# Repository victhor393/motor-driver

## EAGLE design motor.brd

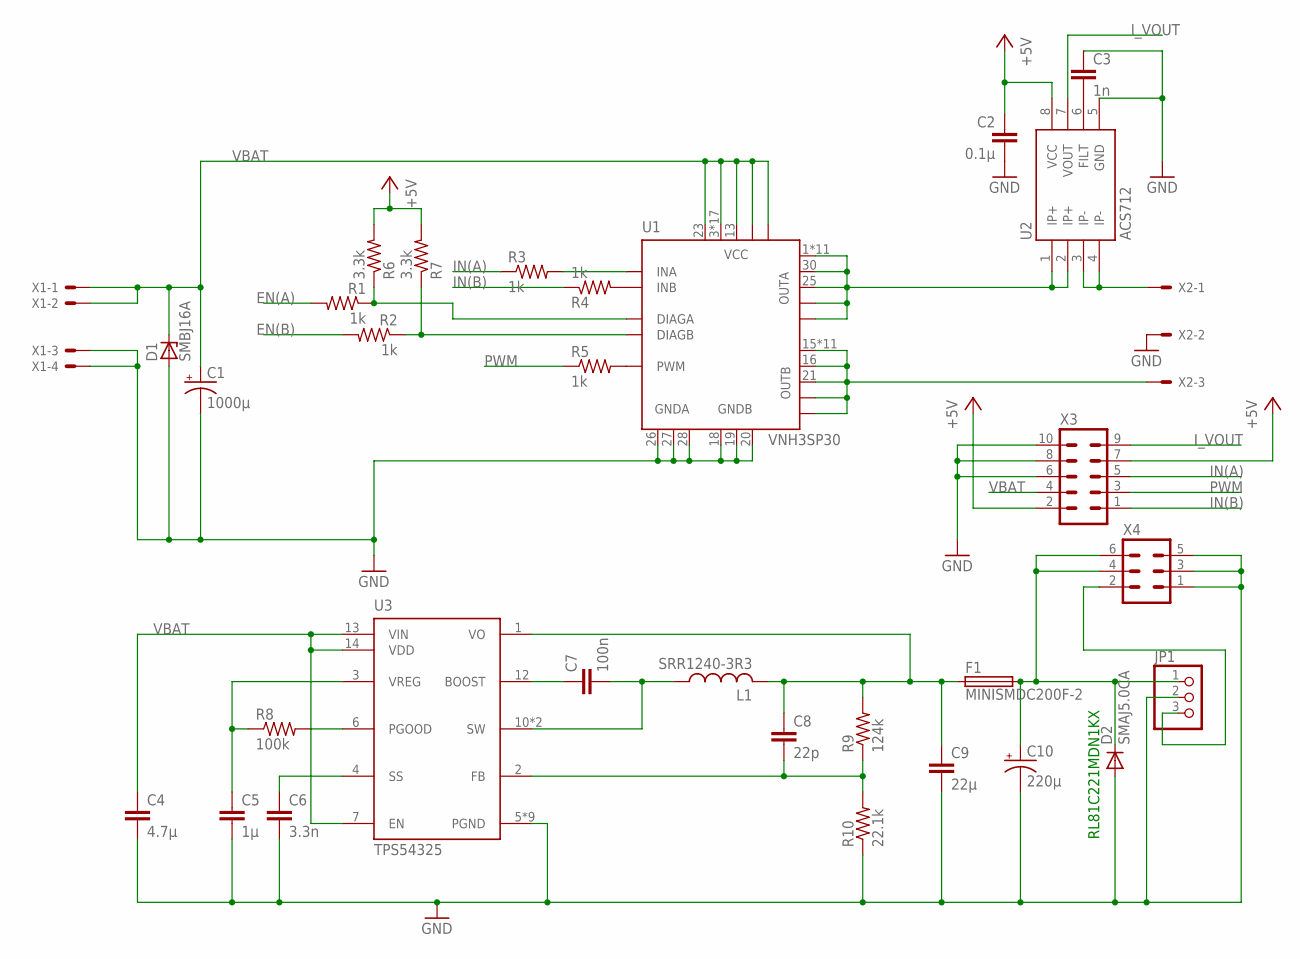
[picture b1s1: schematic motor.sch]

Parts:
C1: 1000µ; E5-13
C2: 0.1µ; C0805
C3: 1n; C0805
C4: 4.7µ; C1206
C5: 1µ; C0805
C6: 3.3n; C0805
C7: 100n; C0805
C8: 22p; C0805
C9: 22µ; C3225
C10: 220µ; E3,5-8
D1: SMBJ16A; SMB
D2: SMAJ5.0CA; DO-214AC
F1: MINISMDC200F-2; MINISMDC200F
JP1: PINHD-1X3; 1X03
L1: SRR1240-3R3; HCM1103
R1, R2, R3, R4, R5: 1k; R0805
R6, R7: 3.3k; R0805
R8: 100k; R0805
R9: 124k; R0805
R10: 22.1k; R0805
U1: VNH3SP30; MULTIPOWERSO-30
U2: ACS712; SO08
U3: TPS54325; HTSSOP14PWP
X1: KK-156-4
X2: KK-156-3
X3: ML10
X4: ML6

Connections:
+5V: C2.1, R6.2, R7.2, U2.8 (VCC), X3.2, X3.7
+5V/S: C8.1, C9.1, F1.1, L1.P$2 (2), R9.2, U3.1 (VO)
EN(A): R1.2
EN(B): R2.2
GND: C1.-, C2.2, C3.1, C4.2, C5.2, C6.2, C9.2, C10.-, D1.A, D2.A, JP1.2, R10.1, U1.18 (GNDB), U1.19 (GNDB), U1.20 (GNDB), U1.26 (GNDA), U1.27 (GNDA), U1.28 (GNDA), U2.5 (GND), U3.5 (PGND), U3.8 (PGND), U3.9 (PGND), U3.EXP (PGND), U3.EXP1 (PGND), U3.P$1 (PGND), U3.P$2 (PGND), U3.P$3 (PGND), U3.P$4 (PGND), X1.3, X1.4, X2.2, X3.6, X3.8, X3.10, X4.1, X4.3, X4.5
IN(A): R3.1, X3.5
IN(B): R4.1, X3.1
I_VOUT: U2.7 (VOUT), X3.9
unnamed: U1.15 (OUTB), U1.16 (OUTB), U1.21 (OUTB), U1.OUTB, U1.OUTB1 (OUTB), U1.OUTB2 (OUTB), U1.OUTB3 (OUTB), U1.OUTB4 (OUTB), U1.OUTB5 (OUTB), U1.OUTB6 (OUTB), U1.OUTB7 (OUTB), U1.OUTB8 (OUTB), U1.OUTB9 (OUTB), U1.OUTB10 (OUTB), U1.OUTB@1 (OUTB), X2.3
unnamed: U1.1 (OUTA), U1.25 (OUTA), U1.30 (OUTA), U1.OUTA, U1.OUTA1 (OUTA), U1.OUTA2 (OUTA), U1.OUTA3 (OUTA), U1.OUTA4 (OUTA), U1.OUTA5 (OUTA), U1.OUTA6 (OUTA), U1.OUTA7 (OUTA), U1.OUTA8 (OUTA), U1.OUTA9 (OUTA), U1.OUTA10 (OUTA), U1.OUTA@1 (OUTA), U2.1 (IP+), U2.2 (IP+)
unnamed: R3.2, U1.5 (INA)
unnamed: R4.2, U1.11 (INB)
unnamed: R8.2, U3.6 (PGOOD)
unnamed: R1.1, R6.1, U1.6 (DIAGA)
unnamed: R2.1, R7.1, U1.10 (DIAGB)
unnamed: U2.3 (IP-), U2.4 (IP-), X2.1
unnamed: C5.1, R8.1, U3.3 (VREG)
unnamed: C3.2, U2.6 (FILT)
unnamed: C6.1, U3.4 (SS)
unnamed: C7.1, U3.12 (BOOST)
unnamed: C7.2, L1.P$1 (1), U3.10 (SW), U3.11 (SW)
unnamed: C8.2, R9.1, R10.2, U3.2 (FB)
unnamed: C10.+, D2.C, F1.2, JP1.1, X4.4, X4.6
unnamed: R5.2, U1.8 (PWM)
PWM: R5.1, X3.3
S_CTL: JP1.3, X4.2
VBAT: C1.+, C4.1, D1.C, U1.3 (VCC), U1.13 (VCC), U1.23 (VCC), U1.VCC, U1.VCC1 (VCC), U1.VCC2 (VCC), U1.VCC3 (VCC), U1.VCC4 (VCC), U1.VCC5 (VCC), U1.VCC6 (VCC), U1.VCC7 (VCC), U1.VCC8 (VCC), U1.VCC9 (VCC), U1.VCC10 (VCC), U1.VCC11 (VCC), U1.VCC12 (VCC), U1.VCC13 (VCC), U1.VCC14 (VCC), U1.VCC15 (VCC), U1.VCC16 (VCC), U1.VCC@1 (VCC), U3.7 (EN), U3.13 (VIN), U3.14 (VDD), X1.1, X1.2, X3.4

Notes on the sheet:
RL81C221MDN1KX

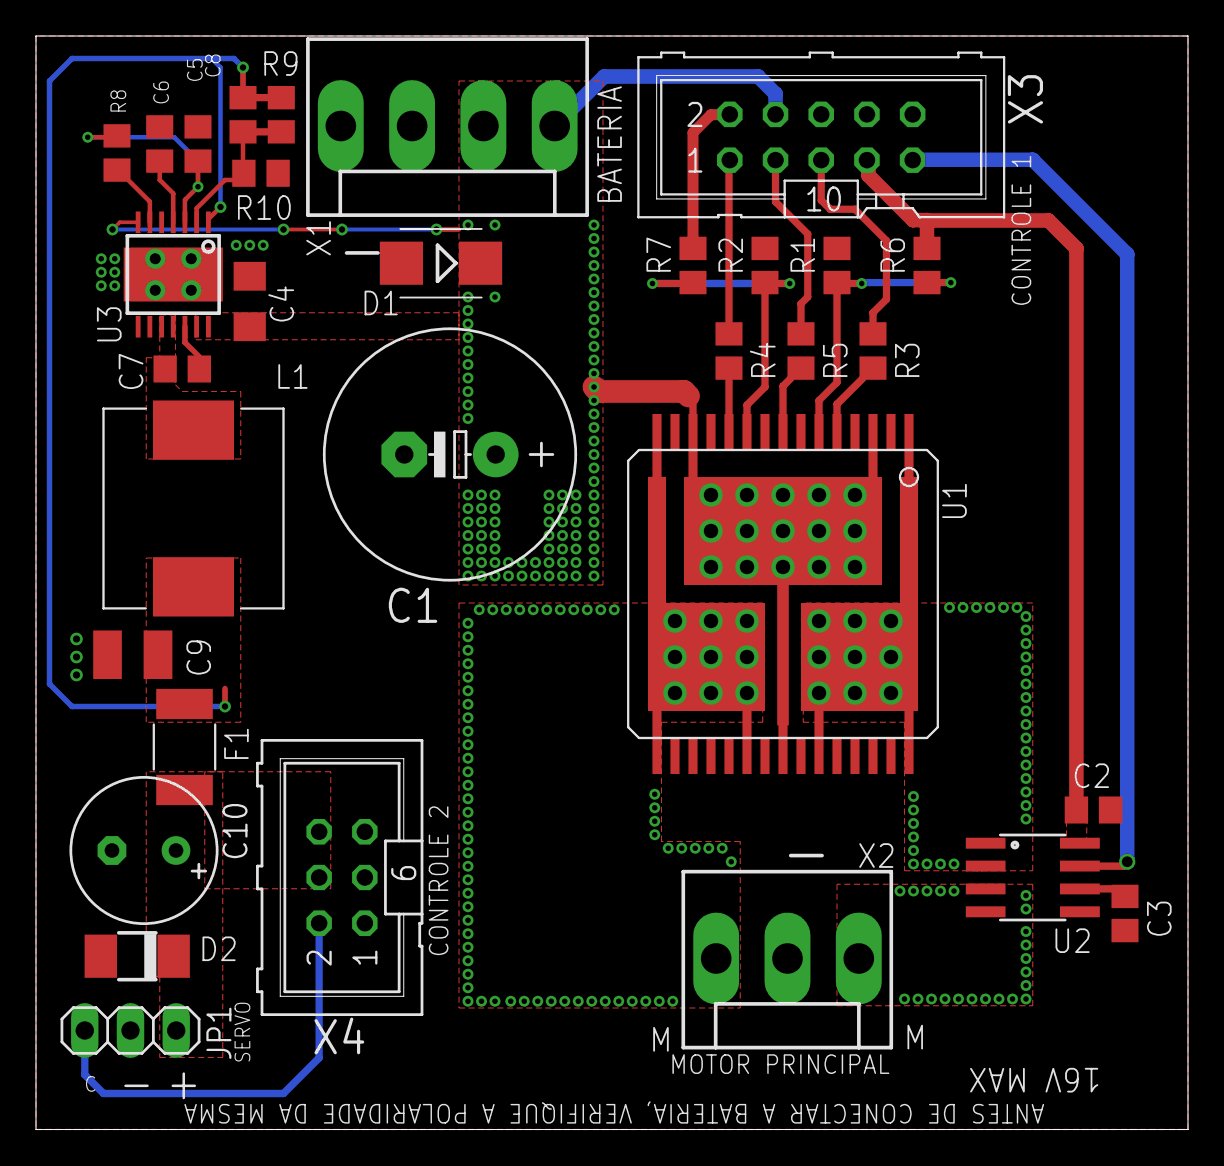
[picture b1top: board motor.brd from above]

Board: 2 copper layers, 64.0 x 60.8 mm, 32 parts (0 on the bottom side), 25 nets.

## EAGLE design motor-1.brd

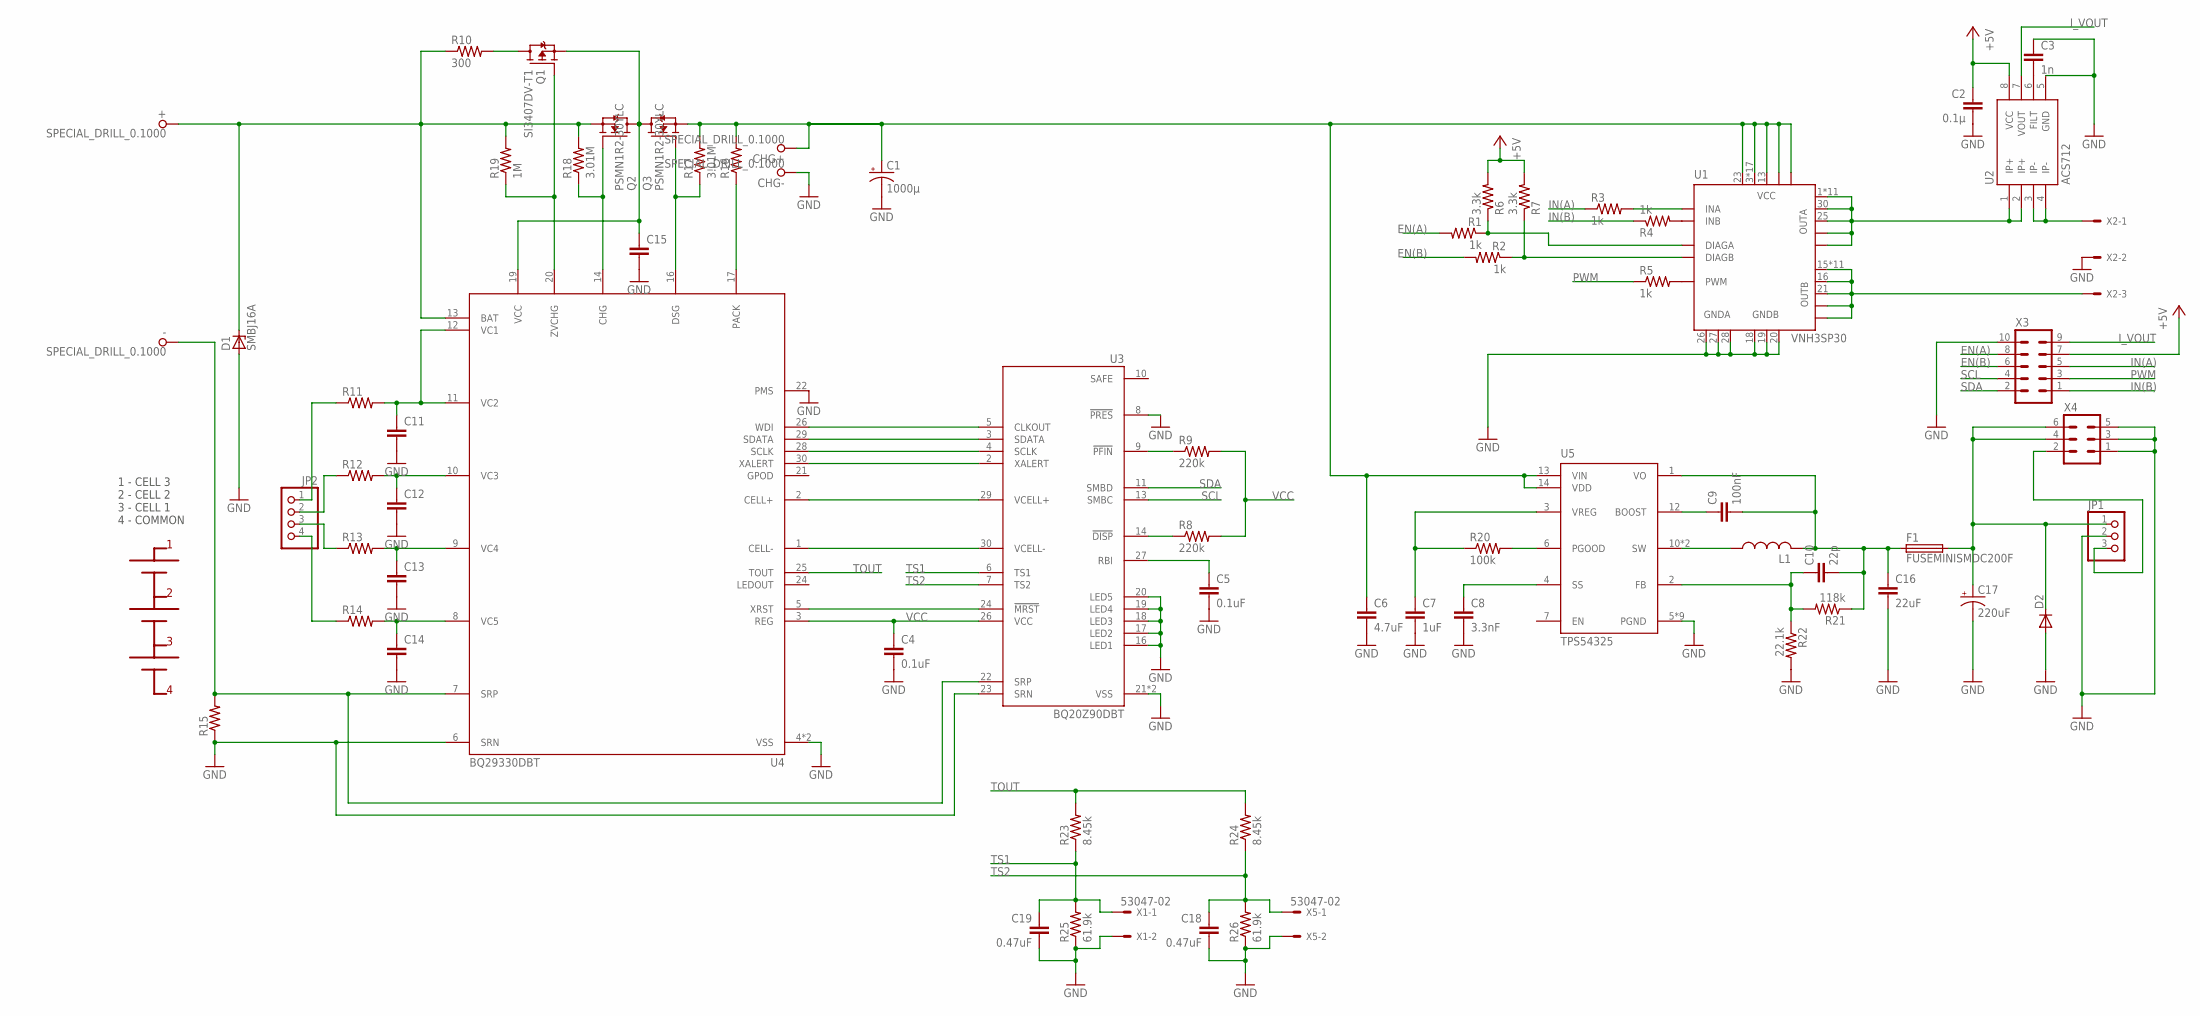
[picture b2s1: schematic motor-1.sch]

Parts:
+: SPECIAL_DRILL_0.1000; PAD_0.1000
-: SPECIAL_DRILL_0.1000; PAD_0.1000
C1: 1000µ; E5-13
C2: 0.1µ; C0805
C3: 1n; C0805
C4, C5: 0.1uF; C0603
C6: 4.7uF; C1206
C7: 1uF; C0805
C8: 3.3nF; C0805
C9: 100nF; C0805
C10: 22p; C0805
C11, C12, C13, C14, C15: C-EUC0603; C0603
C16: 22uF; C3225
C17: 220uF; E3,5-8
C18, C19: 0.47uF; C0603
CHG+: SPECIAL_DRILL_0.1000; PAD_0.1000
CHG-: SPECIAL_DRILL_0.1000; PAD_0.1000
D1: SMBJ16A; SMB
D2: DIODE-DO214AC; DO214AC
F1: FUSEMINISMDC200F; MINISMDC200F
JP1: PINHD-1X3; 1X03
JP2: PINHD-1X4; 1X04
L1: L-USXAL50XX; XAL50XX
Q1: SI3407DV-T1; SOT23-6
Q2, Q3: PSMN1R2-30YLC; LFPAK
R1, R2, R3, R4, R5: 1k; R0805
R6, R7: 3.3k; R0805
R8, R9: 220k; R0603
R10: 300; R2512
R11, R12, R13, R14, R16: R-US_R0603; R0603
R15: R-US_R1210; R1210
R17, R18: 3.01M; R0603
R19: 1M; R0603
R20: 100k; R0805
R21: 118k; R0805
R22: 22.1k; R0805
R23, R24: 8.45k; R0603
R25, R26: 61.9k; R0603
U1: VNH3SP30; MULTIPOWERSO-30
U2: ACS712; SO08
U3: BQ20Z90DBT; DBT_R-PDSO-G30
U4: BQ29330DBT; DBT_R-PDSO-G30
U5: TPS54325; HTSSOP14PWP
X1, X5: 53047-02
X2: KK-156-3
X3: ML10
X4: ML6

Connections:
+5V: C2.1, R6.2, R7.2, U2.8 (VCC), X3.7
EN(A): R1.2, X3.8
EN(B): R2.2, X3.6
GND: C1.-, C2.2, C3.1, C4.2, C5.2, C6.2, C7.2, C8.2, C11.2, C12.2, C13.2, C14.2, C15.2, C16.2, C17.-, C18.2, C19.2, CHG-.1, D1.A, D2.A, JP1.2, R15.1, R22.2, R25.1, R26.1, U1.18 (GNDB), U1.19 (GNDB), U1.20 (GNDB), U1.26 (GNDA), U1.27 (GNDA), U1.28 (GNDA), U2.5 (GND), U3.8 (!PRES), U3.16 (LED1), U3.17 (LED2), U3.18 (LED3), U3.19 (LED4), U3.20 (LED5), U3.21 (VSS), U3.23 (SRN), U3.25 (VSS), U4.4 (VSS), U4.6 (SRN), U4.22 (PMS), U4.23 (VSS), U5.5 (PGND), U5.8 (PGND), U5.9 (PGND), U5.EXP (PGND), U5.EXP1 (PGND), U5.P$1 (PGND), U5.P$2 (PGND), U5.P$3 (PGND), U5.P$4 (PGND), X1.2, X2.2, X3.10, X4.1, X4.3, X4.5, X5.2
GND_P: -.1, R15.2, U3.22 (SRP), U4.7 (SRP)
IN(A): R3.1, X3.5
IN(B): R4.1, X3.1
I_VOUT: U2.7 (VOUT), X3.9
unnamed: U1.15 (OUTB), U1.16 (OUTB), U1.21 (OUTB), U1.OUTB, U1.OUTB1 (OUTB), U1.OUTB2 (OUTB), U1.OUTB3 (OUTB), U1.OUTB4 (OUTB), U1.OUTB5 (OUTB), U1.OUTB6 (OUTB), U1.OUTB7 (OUTB), U1.OUTB8 (OUTB), U1.OUTB9 (OUTB), U1.OUTB10 (OUTB), U1.OUTB@1 (OUTB), X2.3
unnamed: U1.1 (OUTA), U1.25 (OUTA), U1.30 (OUTA), U1.OUTA, U1.OUTA1 (OUTA), U1.OUTA2 (OUTA), U1.OUTA3 (OUTA), U1.OUTA4 (OUTA), U1.OUTA5 (OUTA), U1.OUTA6 (OUTA), U1.OUTA7 (OUTA), U1.OUTA8 (OUTA), U1.OUTA9 (OUTA), U1.OUTA10 (OUTA), U1.OUTA@1 (OUTA), U2.1 (IP+), U2.2 (IP+)
unnamed: R3.2, U1.5 (INA)
unnamed: R4.2, U1.11 (INB)
unnamed: U3.5 (CLKOUT), U4.26 (WDI)
unnamed: R1.1, R6.1, U1.6 (DIAGA)
unnamed: R2.1, R7.1, U1.10 (DIAGB)
unnamed: U2.3 (IP-), U2.4 (IP-), X2.1
unnamed: U3.3 (SDATA), U4.29 (SDATA)
unnamed: C3.2, U2.6 (FILT)
unnamed: U3.4 (SCLK), U4.28 (SCLK)
unnamed: U3.2 (XALERT), U4.30 (XALERT)
unnamed: U3.29 (VCELL+), U4.2 (CELL+)
unnamed: U3.30 (VCELL-), U4.1 (CELL-)
unnamed: U3.24 (!MRST), U4.5 (XRST)
unnamed: C17.+, D2.C, F1.2, JP1.1, X4.4, X4.6
unnamed: R5.2, U1.8 (PWM)
unnamed: JP2.2, R12.1
unnamed: JP2.1, R11.1
unnamed: C11.1, R11.2, U4.11 (VC2), U4.12 (VC1)
unnamed: C12.1, R12.2, U4.10 (VC3)
unnamed: JP2.3, R13.1
unnamed: C13.1, R13.2, U4.9 (VC4)
unnamed: JP2.4, R14.1
unnamed: C14.1, R14.2, U4.8 (VC5)
unnamed: R16.1, U4.17 (PACK)
unnamed: Q1.1 (D1), Q1.2 (D1), Q1.5 (D1), Q1.6 (D1), R10.2
unnamed: C5.1, U3.27 (RBI)
unnamed: Q3.4 (G), R17.1, U4.16 (DSG)
unnamed: C15.1, Q1.4 (S1), Q2.P$1 (D), Q2.P$2 (D), Q2.P$3 (D), Q3.P$1 (D), Q3.P$2 (D), Q3.P$3 (D), U4.19 (VCC)
unnamed: Q2.4 (G), R18.1, U4.14 (CHG)
unnamed: Q1.3 (G1), R19.1, U4.20 (ZVCHG)
unnamed: +.1, D1.C, Q2.1 (S), Q2.2 (S), Q2.3 (S), R10.1, R18.2, R19.2, U4.13 (BAT)
unnamed: R8.1, U3.14 (!DISP)
unnamed: R9.1, U3.9 (!PFIN)
unnamed: C7.1, R20.1, U5.3 (VREG)
unnamed: R20.2, U5.6 (PGOOD)
unnamed: C8.1, U5.4 (SS)
unnamed: L1.1, U5.10 (SW), U5.11 (SW)
unnamed: C9.2, C10.2, C16.1, F1.1, L1.2, R21.1, U5.1 (VO)
unnamed: C9.1, U5.12 (BOOST)
unnamed: C10.1, R21.2, R22.1, U5.2 (FB)
PWM: R5.1, X3.3
SCL: U3.13 (SMBC), X3.4
SDA: U3.11 (SMBD), X3.2
S_CTL: JP1.3, X4.2
TOUT: R23.2, R24.2, U4.25 (TOUT)
TS1: C19.1, R23.1, R25.2, U3.6 (TS1), X1.1
TS2: C18.1, R24.1, R26.2, U3.7 (TS2), X5.1
VBAT: C1.+, C6.1, CHG+.1, Q3.1 (S), Q3.2 (S), Q3.3 (S), R16.2, R17.2, U1.3 (VCC), U1.13 (VCC), U1.23 (VCC), U1.VCC, U1.VCC1 (VCC), U1.VCC2 (VCC), U1.VCC3 (VCC), U1.VCC4 (VCC), U1.VCC5 (VCC), U1.VCC6 (VCC), U1.VCC7 (VCC), U1.VCC8 (VCC), U1.VCC9 (VCC), U1.VCC10 (VCC), U1.VCC11 (VCC), U1.VCC12 (VCC), U1.VCC13 (VCC), U1.VCC14 (VCC), U1.VCC15 (VCC), U1.VCC16 (VCC), U1.VCC@1 (VCC), U5.13 (VIN), U5.14 (VDD)
VCC: C4.1, R8.2, R9.2, U3.26 (VCC), U4.3 (REG)

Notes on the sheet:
1 - CELL 3 2 - CELL 2 3 - CELL 1 4 - COMMON

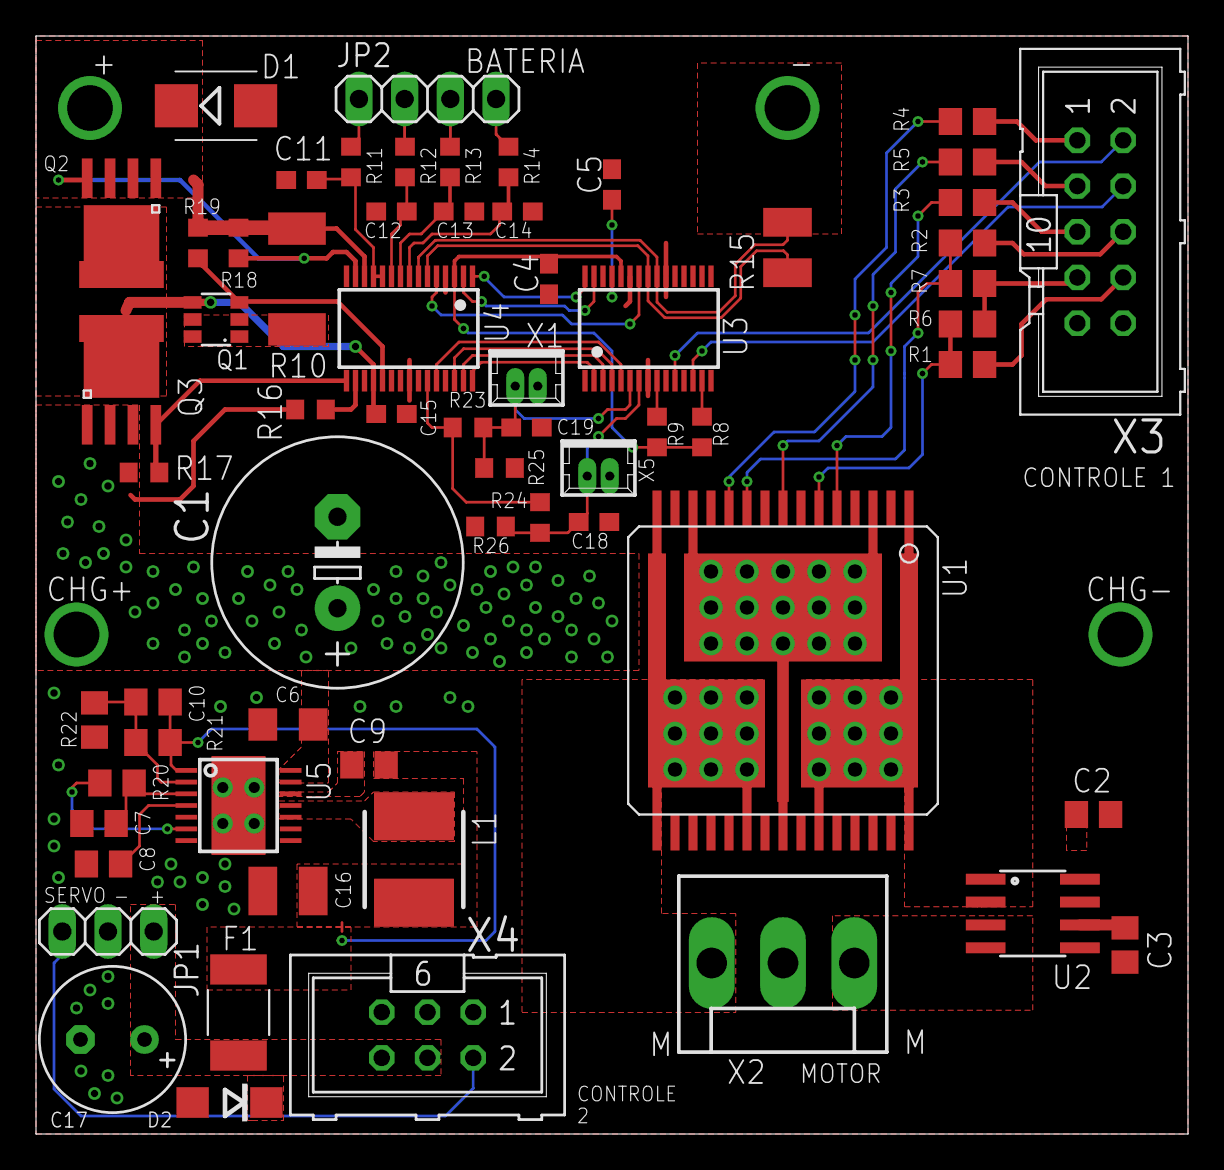
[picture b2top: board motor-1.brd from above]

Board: 2 copper layers, 64.0 x 61.0 mm, 68 parts (0 on the bottom side), 59 nets.

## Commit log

2019-05-12 Initial commit fix
2019-05-21 Added schematic and board layout in pdf format

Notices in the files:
parts and their libraries:
SparkFun-AnalogIC: Licensing: CC v3.0 Share-Alike You are welcome to use this library for commercial purposes.
